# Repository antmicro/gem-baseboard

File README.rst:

GEM Demo Board
==============

Copyright (c) 2020 `Antmicro <https://www.antmicro.com>`_

.. image:: https://img.shields.io/badge/View%20on-Antmicro%20Open%20Source%20Portal-332d37?style=flat-square
      :target: https://opensource.antmicro.com/projects/gem-baseboard
   
.. figure:: img/gem-demo-board.png

This repository contains PCB design files for a demo board compatible with the `GEM1 <https://github.com/antmicro/gem1-adapter>`_ and `GEM2 <https://github.com/antmicro/gem2-adapter>`_ adapter boards.

The board acts as an evaluation carrier board for the GEM adapter boards.
It includes a 4-channel FTDI USB/MPSSE converter that can be used for configuring the chiplets inside the GEM designs from an external host PC using a single USB connection and the MPSSE engine built into the FTDI controller.

The board contains two FFC connectors supporting MIPI CSI input and output.
The FFC connectors are pin-compatible with the Raspberry Pi camera interface.
It is possible to connect a Raspberry Pi camera module to the input connector on the board and provide processed CSI data back on the output CSI FFC.
It is also possible to configure the board as an expansion hat for the Raspberry Pi platform.
For more details regarding the supported connection scenarios please refer to the respective schematic sheets.

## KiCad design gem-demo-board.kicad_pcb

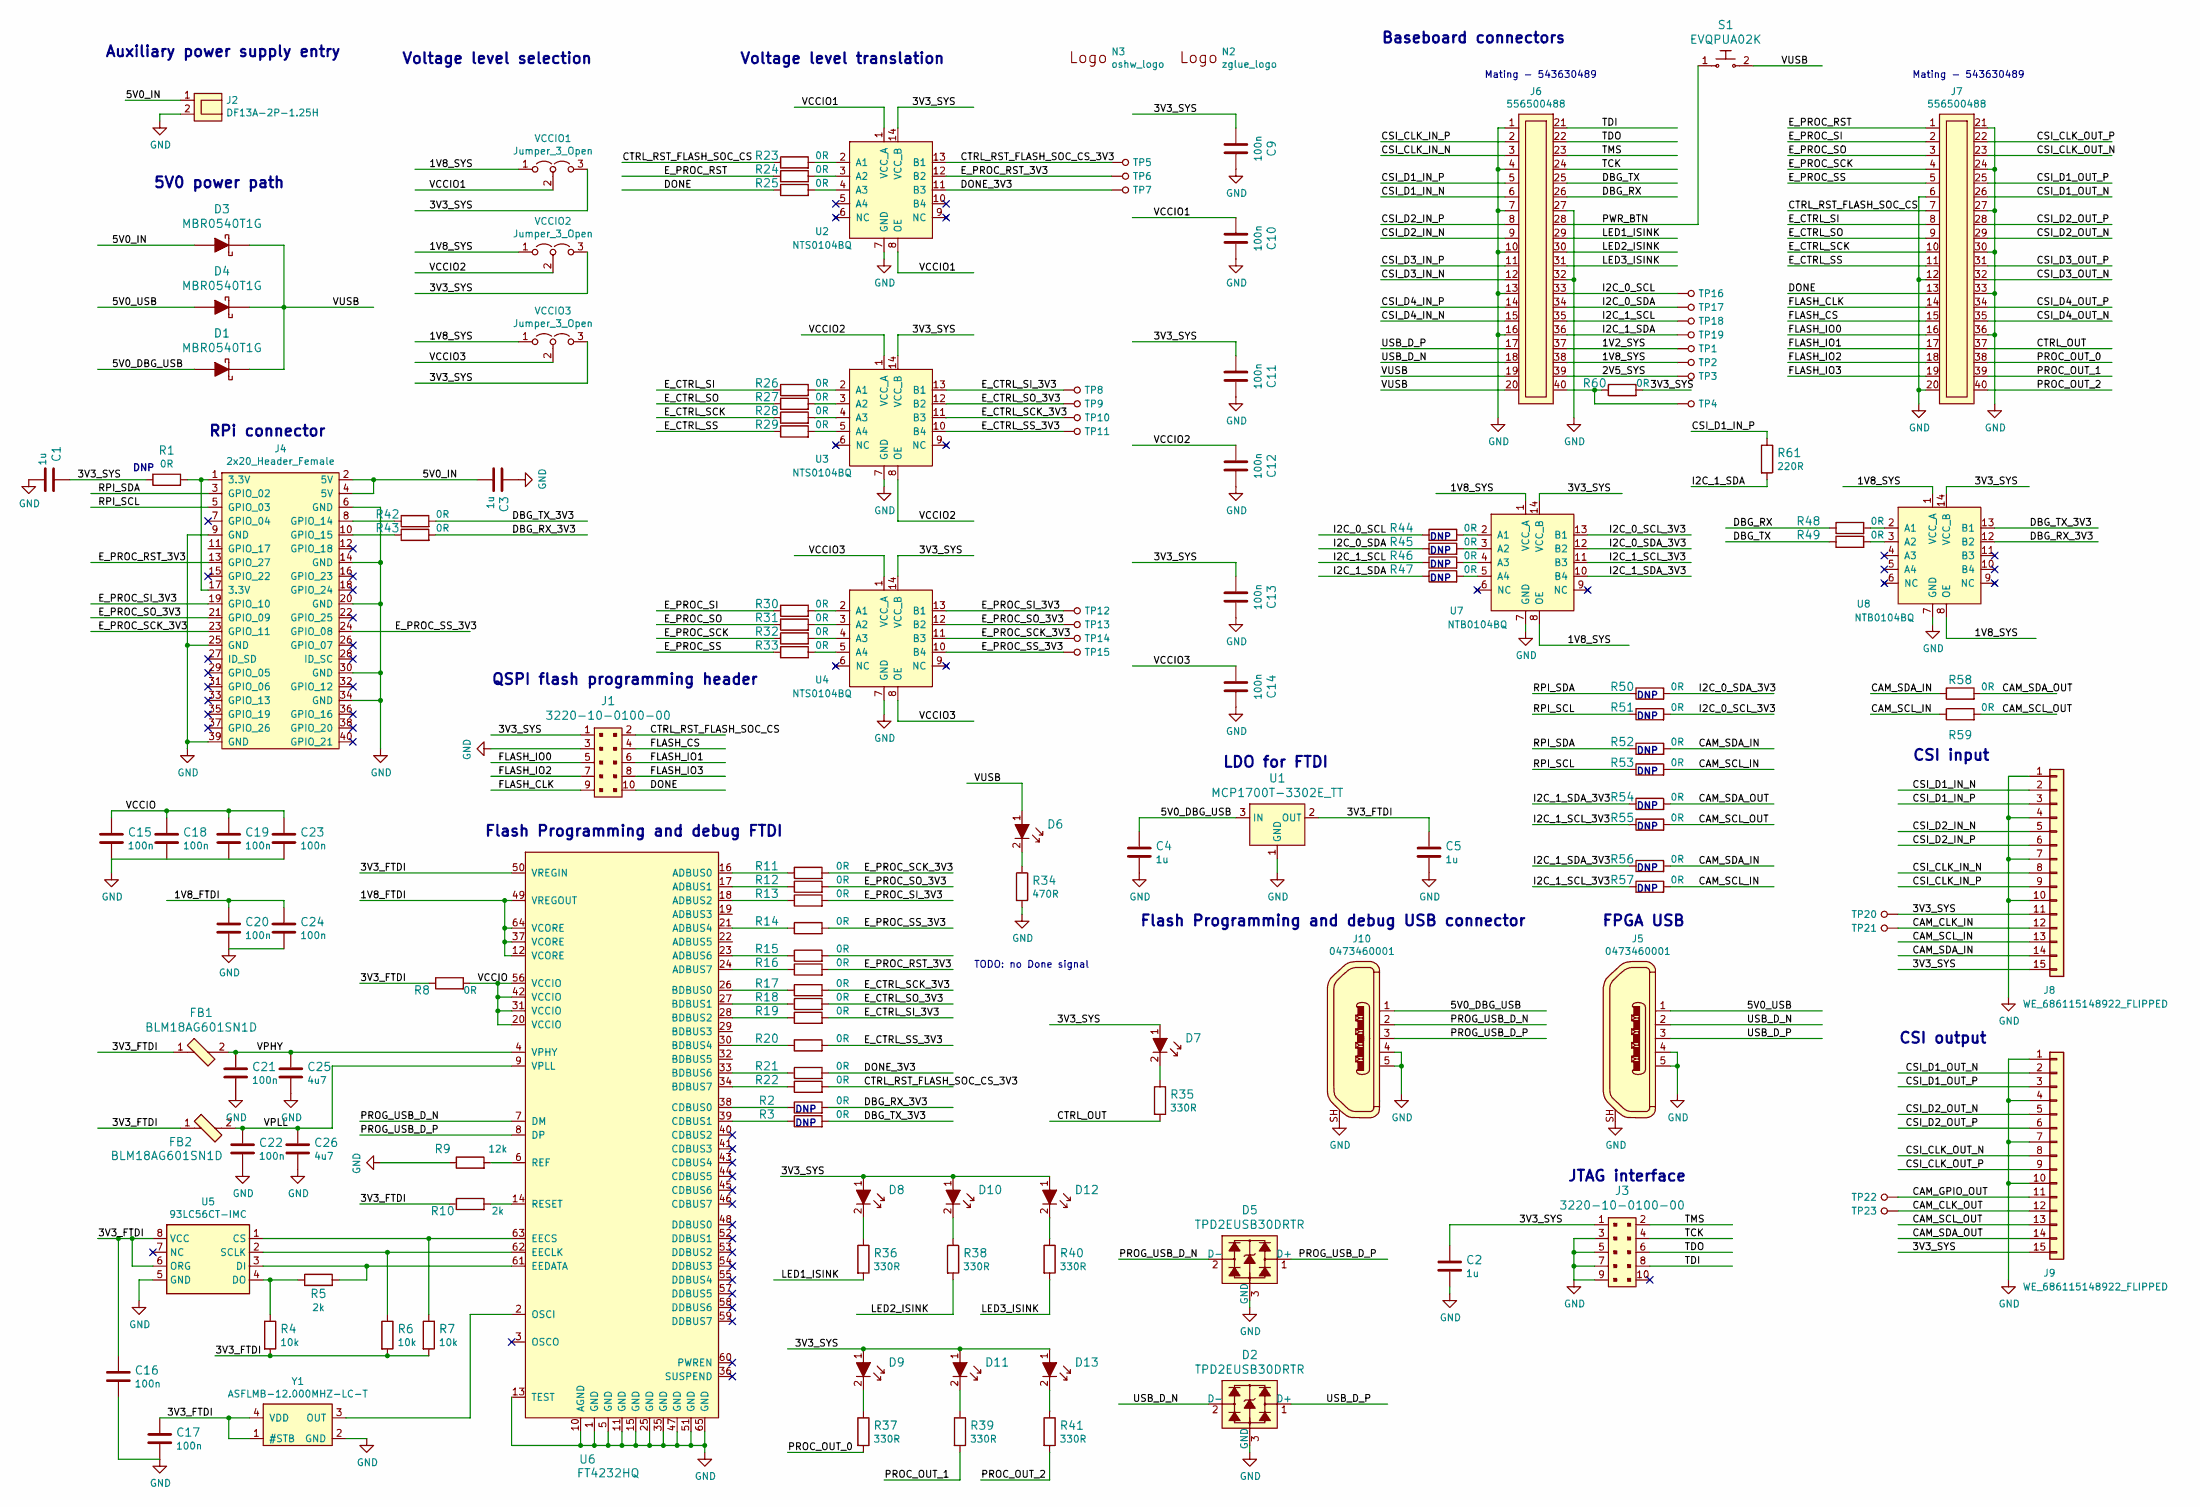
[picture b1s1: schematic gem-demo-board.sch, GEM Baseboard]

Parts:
C1, C2, C3, C4, C5: C_1u_0603; 0603-cap; MPN 0603X105K160CT
C9, C10, C11, C12, C13, C14, C15, C16, C17, C18, C19, C20, C21, C22, C23, C24: C_100n_0402_6V3; 0402-cap; MPN 0402X104K6R3CT
C25, C26: C_4u7_0402; 0402-cap; MPN GRM155R60G475ME
D1, D3, D4: MBR0540T1G; SOD-123; MPN MBR0540T1G
D2, D5: TPD2EUSB30DRTR; SOT-3; MPN TPD2EUSB30DRTR
D6, D7, D8, D9, D10, D11, D12, D13: LG_L29K-G2J1-24-Z; LED_0603; MPN LG L29K-G2J1-24-Z
FB1, FB2: BLM18AG601SN1D; 0603; MPN BLM18AG601SN1D
J1, J3: 3220-10-0100-00; PinHeader_2x5_P1.27mm_Drill.7mm; MPN 3220-10-0100-00
J2: DF13A-2P-1.25H; MPN DF13A-2P-1.25H
J4: 2x20_Header_Female; PinHeader_2x40_P2.54_Drill1mm; MPN 2214S-40SG-85
J5, J10: 0473460001; USB_Micro_B_Female_0473460001; MPN 0473460001
J6, J7: 556500488; MPN 556500488
J8, J9: WE_686115148922_FLIPPED; MPN 686115148922
N2: zglue_logo; zglue-logo
N3: oshw_logo; oshw-logo
R1: R_0R_0603; 0603-res; MPN CR0603-J/-000ELF
R2, R3, R8, R11, R12, R13, R14, R15, R16, R17, R18, R19, R20, R21, R22, R23, R24, R25, R26, R27, R28, R29, R30, R31, R32, R33, R42, R43, R44, R45, R46, R47, R48, R49, R50, R51, R52, R53, R54, R55, R56, R57, R58, R59, R60: R_0R_0402; 0402-res; MPN ERJ2GE0R00X
R4, R6, R7: R_10k_0402; 0402-res; MPN CRCW040210K0FKEDHP
R5, R10: R_2k_0402; 0402-res; MPN CRCW04022K00FKED
R9: R_12k_0402; 0402-res; MPN CRCW040212K0FKEDHP
R34: R_470R_0402; 0402-res; MPN CRCW0402470RFKED.
R35, R36, R37, R38, R39, R40, R41: R_330R_0402; 0402-res; MPN MCMR04X3300FTL
R61: R_220R_0402; 0402-res; MPN CRG0402J220R
S1: EVQPUA02K; Panasonic_EVQPUJ_EVQPUA; MPN EVQPUA02K
TP1, TP2, TP3, TP4, TP5, TP6, TP7, TP8, TP9, TP10, TP11, TP12, TP13, TP14, TP15, TP16, TP17, TP18, TP19, TP20, TP21, TP22, TP23: TP_SMD1MM; Testpoint_smd_1mm
U1: MCP1700T-3302E_TT; SOT-23-3; MPN MCP1700T-3302E/TT
U2, U3, U4: NTS0104BQ; QDHVQFN14; MPN NTS0104BQ
U5: 93LC56CT-IMC; DFN-8_2x3mm; MPN 93LC56CT-I/MC
U6: FT4232HQ; MPN FT4232HQ
U7, U8: NTB0104BQ; QDHVQFN14; MPN NTB0104BQ
VCCIO1, VCCIO2, VCCIO3: Jumper_3_Open; SolderJumper-3_P1.3mm_Open_Pad1.0x1.5mm
Y1: ASFLMB-12.000MHZ-LC-T; ASFLMB; MPN ASFLMB-12.000MHZ-LC-T

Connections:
/1V2_SYS: J6.37, TP1.1
/1V8_FTDI: C20.1, C24.1, U6.12 (VCORE), U6.37 (VCORE), U6.49 (VREGOUT), U6.64 (VCORE)
/1V8_SYS: J6.38, TP2.1, U7.1 (VCC_A), U7.8 (OE), U8.1 (VCC_A), U8.8 (OE), VCCIO1.1 (A), VCCIO2.1 (A), VCCIO3.1 (A)
/2V5_SYS: J6.39, TP3.1
/3V3_FTDI: C5.1, C16.1, C17.1, FB1.1, FB2.1, R4.2, R6.2, R7.2, R8.1, R10.1, U1.2 (OUT), U5.6 (ORG), U5.8 (VCC), U6.50 (VREGIN), Y1.1 (#STB), Y1.4 (VDD)
/3V3_SYS: C1.1, C2.1, C9.2, C11.2, C13.2, D7.1, D8.1, D9.1, D10.1, D11.1, D12.1, D13.1, J1.1, J3.1, J8.11, J8.15, J9.15, R1.1, R60.2, TP20.1, U2.14 (VCC_B), U3.14 (VCC_B), U4.14 (VCC_B), U7.14 (VCC_B), U8.14 (VCC_B), VCCIO1.3 (B), VCCIO2.3 (B), VCCIO3.3 (B)
/5V0_DBG_USB: C4.1, D1.A, J10.1, U1.3 (IN)
/5V0_IN: C3.2, D3.A, J2.1, J4.2 (5V), J4.4 (5V)
/5V0_USB: D4.A, J5.1
/CAM_CLK_IN: J8.12, TP21.1
/CAM_CLK_OUT: J9.12, TP23.1
/CAM_GPIO_OUT: J9.11, TP22.1
/CAM_SCL_IN: J8.13, R53.2, R57.2, R59.1
/CAM_SCL_OUT: J9.13, R55.2, R59.2
/CAM_SDA_IN: J8.14, R52.2, R56.2, R58.1
/CAM_SDA_OUT: J9.14, R54.2, R58.2
/CSI_CLK_IN_N: J6.3, J8.8
/CSI_CLK_IN_P: J6.2, J8.9
/CSI_CLK_OUT_N: J7.23, J9.8
/CSI_CLK_OUT_P: J7.22, J9.9
/CSI_D1_IN_N: J6.6, J8.2
/CSI_D1_IN_P: J6.5, J8.3, R61.1
/CSI_D1_OUT_N: J7.26, J9.2
/CSI_D1_OUT_P: J7.25, J9.3
/CSI_D2_IN_N: J6.9, J8.5
/CSI_D2_IN_P: J6.8, J8.6
/CSI_D2_OUT_N: J7.29, J9.5
/CSI_D2_OUT_P: J7.28, J9.6
/CSI_D3_IN_N: J6.12
/CSI_D3_IN_P: J6.11
/CSI_D3_OUT_N: J7.32
/CSI_D3_OUT_P: J7.31
/CSI_D4_IN_N: J6.15
/CSI_D4_IN_P: J6.14
/CSI_D4_OUT_N: J7.35
/CSI_D4_OUT_P: J7.34
/CTRL_OUT: J7.37, R35.2
/CTRL_RST_FLASH_SOC_CS: J1.2, J7.7, R23.1
/CTRL_RST_FLASH_SOC_CS_3V3: R22.2, TP5.1, U2.13 (B1)
/DBG_RX: J6.26, R48.1
/DBG_RX_3V3: R2.2, R43.2, U8.12 (B2)
/DBG_TX: J6.25, R49.1
/DBG_TX_3V3: R3.2, R42.2, U8.13 (B1)
/DONE: J1.10, J7.13, R25.1
/DONE_3V3: R21.2, TP7.1, U2.11 (B3)
/E_CTRL_SCK: J7.10, R28.1
/E_CTRL_SCK_3V3: R17.2, TP10.1, U3.11 (B3)
/E_CTRL_SI: J7.8, R26.1
/E_CTRL_SI_3V3: R19.2, TP8.1, U3.13 (B1)
/E_CTRL_SO: J7.9, R27.1
/E_CTRL_SO_3V3: R18.2, TP9.1, U3.12 (B2)
/E_CTRL_SS: J7.11, R29.1
/E_CTRL_SS_3V3: R20.2, TP11.1, U3.10 (B4)
/E_PROC_RST: J7.1, R24.1
/E_PROC_RST_3V3: J4.13 (GPIO_27), R16.2, TP6.1, U2.12 (B2)
/E_PROC_SCK: J7.4, R32.1
/E_PROC_SCK_3V3: J4.23 (GPIO_11), R11.2, TP14.1, U4.11 (B3)
/E_PROC_SI: J7.2, R30.1
/E_PROC_SI_3V3: J4.19 (GPIO_10), R13.2, TP12.1, U4.13 (B1)
/E_PROC_SO: J7.3, R31.1
/E_PROC_SO_3V3: J4.21 (GPIO_09), R12.2, TP13.1, U4.12 (B2)
/E_PROC_SS: J7.5, R33.1
/E_PROC_SS_3V3: J4.24 (GPIO_08), R14.2, TP15.1, U4.10 (B4)
/FLASH_CLK: J1.9, J7.14
/FLASH_CS: J1.4, J7.15
/FLASH_IO0: J1.5, J7.16
/FLASH_IO1: J1.6, J7.17
/FLASH_IO2: J1.7, J7.18
/FLASH_IO3: J1.8, J7.19
/I2C_0_SCL: J6.33, R44.1, TP16.1
/I2C_0_SCL_3V3: R51.2, U7.13 (B1)
/I2C_0_SDA: J6.34, R45.1, TP17.1
/I2C_0_SDA_3V3: R50.2, U7.12 (B2)
/I2C_1_SCL: J6.35, R46.1, TP18.1
/I2C_1_SCL_3V3: R55.1, R57.1, U7.11 (B3)
/I2C_1_SDA: J6.36, R47.1, R61.2, TP19.1
/I2C_1_SDA_3V3: R54.1, R56.1, U7.10 (B4)
/LED1_ISINK: J6.29, R36.2
/LED2_ISINK: J6.30, R38.2
/LED3_ISINK: J6.31, R40.2
/PROC_OUT_0: J7.38, R37.2
/PROC_OUT_1: J7.39, R39.2
/PROC_OUT_2: J7.40, R41.2
/PROG_USB_D_N: D5.2 (D-), J10.2, U6.7 (DM)
/PROG_USB_D_P: D5.1 (D+), J10.3, U6.8 (DP)
/PWR_BTN: J6.28, S1.1
/RPI_SCL: J4.5 (GPIO_03), R51.1, R53.1
/RPI_SDA: J4.3 (GPIO_02), R50.1, R52.1
/TCK: J3.4, J6.24
/TDI: J3.8, J6.21
/TDO: J3.6, J6.22
/TMS: J3.2, J6.23
/USB_D_N: D2.2 (D-), J5.2, J6.18
/USB_D_P: D2.1 (D+), J5.3, J6.17
/VCCIO: C15.1, C18.1, C19.1, C23.1, R8.2, U6.20 (VCCIO), U6.31 (VCCIO), U6.42 (VCCIO), U6.56 (VCCIO)
/VCCIO1: C10.2, U2.1 (VCC_A), U2.8 (OE), VCCIO1.2 (C)
/VCCIO2: C12.2, U3.1 (VCC_A), U3.8 (OE), VCCIO2.2 (C)
/VCCIO3: C14.2, U4.1 (VCC_A), U4.8 (OE), VCCIO3.2 (C)
/VPHY: C21.1, C25.1, FB1.2, U6.4 (VPHY)
/VPLL: C22.1, C26.1, FB2.2, U6.9 (VPLL)
/VUSB: D1.K, D3.K, D4.K, D6.1, J6.19, J6.20, S1.2
GND: C1.2, C2.2, C3.1, C4.2, C5.2, C9.1, C10.1, C11.1, C12.1, C13.1, C14.1, C15.2, C16.2, C17.2, C20.2, C21.2, C22.2, C23.2, C24.2, C25.2, C26.2, D2.3 (GND), D5.3 (GND), J1.3, J2.2, J3.3, J3.5, J3.7, J3.9, J4.6 (GND), J4.9 (GND), J4.14 (GND), J4.20 (GND), J4.25 (GND), J4.30 (GND), J4.34 (GND), J4.39 (GND), J5.4, J5.5, J5.SH, J6.1, J6.4, J6.7, J6.10, J6.13, J6.16, J6.27, J6.32, J7.6, J7.12, J7.20, J7.21, J7.24, J7.27, J7.30, J7.33, J7.36, J8.1, J8.4, J8.7, J8.10, J9.1, J9.4, J9.7, J9.10, J10.4, J10.5, J10.SH, R9.1, R34.2, U1.1 (GND), U2.7 (GND), U3.7 (GND), U4.7 (GND), U5.5 (GND), U6.1 (GND), U6.5 (GND), U6.10 (AGND), U6.11 (GND), U6.13 (TEST), U6.15 (GND), U6.25 (GND), U6.35 (GND), U6.47 (GND), U6.51 (GND), U6.65 (GND), U7.7 (GND), U8.7 (GND), Y1.2 (GND)
unnamed: D6.2, R34.1
unnamed: D7.2, R35.1
unnamed: D8.2, R36.1
unnamed: D9.2, R37.1
unnamed: D10.2, R38.1
unnamed: D11.2, R39.1
unnamed: D12.2, R40.1
unnamed: D13.2, R41.1
unnamed: J4.1 (3.3V), J4.17 (3.3V), R1.2
unnamed: J4.8 (GPIO_14), R42.1
unnamed: J4.10 (GPIO_15), R43.1
unnamed: J6.40, R60.1, TP4.1
unnamed: R2.1, U6.38 (CDBUS0)
unnamed: R3.1, U6.39 (CDBUS1)
unnamed: R4.1, R5.1, U5.4 (DO)
unnamed: R5.2, U5.3 (DI), U6.61 (EEDATA)
unnamed: R6.1, U5.2 (SCLK), U6.62 (EECLK)
unnamed: R7.1, U5.1 (CS), U6.63 (EECS)
unnamed: R9.2, U6.6 (REF)
unnamed: R10.2, U6.14 (RESET)
unnamed: R11.1, U6.16 (ADBUS0)
unnamed: R12.1, U6.17 (ADBUS1)
unnamed: R13.1, U6.18 (ADBUS2)
unnamed: R14.1, U6.21 (ADBUS4)
unnamed: R15.1, U6.23 (ADBUS6)
unnamed: R16.1, U6.24 (ADBUS7)
unnamed: R17.1, U6.26 (BDBUS0)
unnamed: R18.1, U6.27 (BDBUS1)
unnamed: R19.1, U6.28 (BDBUS2)
unnamed: R20.1, U6.30 (BDBUS4)
unnamed: R21.1, U6.33 (BDBUS6)
unnamed: R22.1, U6.34 (BDBUS7)
unnamed: R23.2, U2.2 (A1)
unnamed: R24.2, U2.3 (A2)
unnamed: R25.2, U2.4 (A3)
unnamed: R26.2, U3.2 (A1)
unnamed: R27.2, U3.3 (A2)
unnamed: R28.2, U3.4 (A3)
unnamed: R29.2, U3.5 (A4)
unnamed: R30.2, U4.2 (A1)
unnamed: R31.2, U4.3 (A2)
unnamed: R32.2, U4.4 (A3)
unnamed: R33.2, U4.5 (A4)
unnamed: R44.2, U7.2 (A1)
unnamed: R45.2, U7.3 (A2)
unnamed: R46.2, U7.4 (A3)
unnamed: R47.2, U7.5 (A4)
unnamed: R48.2, U8.2 (A1)
unnamed: R49.2, U8.3 (A2)
unnamed: U6.2 (OSCI), Y1.3 (OUT)

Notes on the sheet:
Baseboard connectors
Auxiliary power supply entry
RPi connector
JTAG interface
FPGA USB
5V0 power path
CSI input
CSI output
Mating - 543630489
Voltage level translation
Flash Programming and debug USB connector
Flash Programming and debug FTDI
TODO: no Done signal
LDO for FTDI
Voltage level selection
QSPI flash programming header
DNP

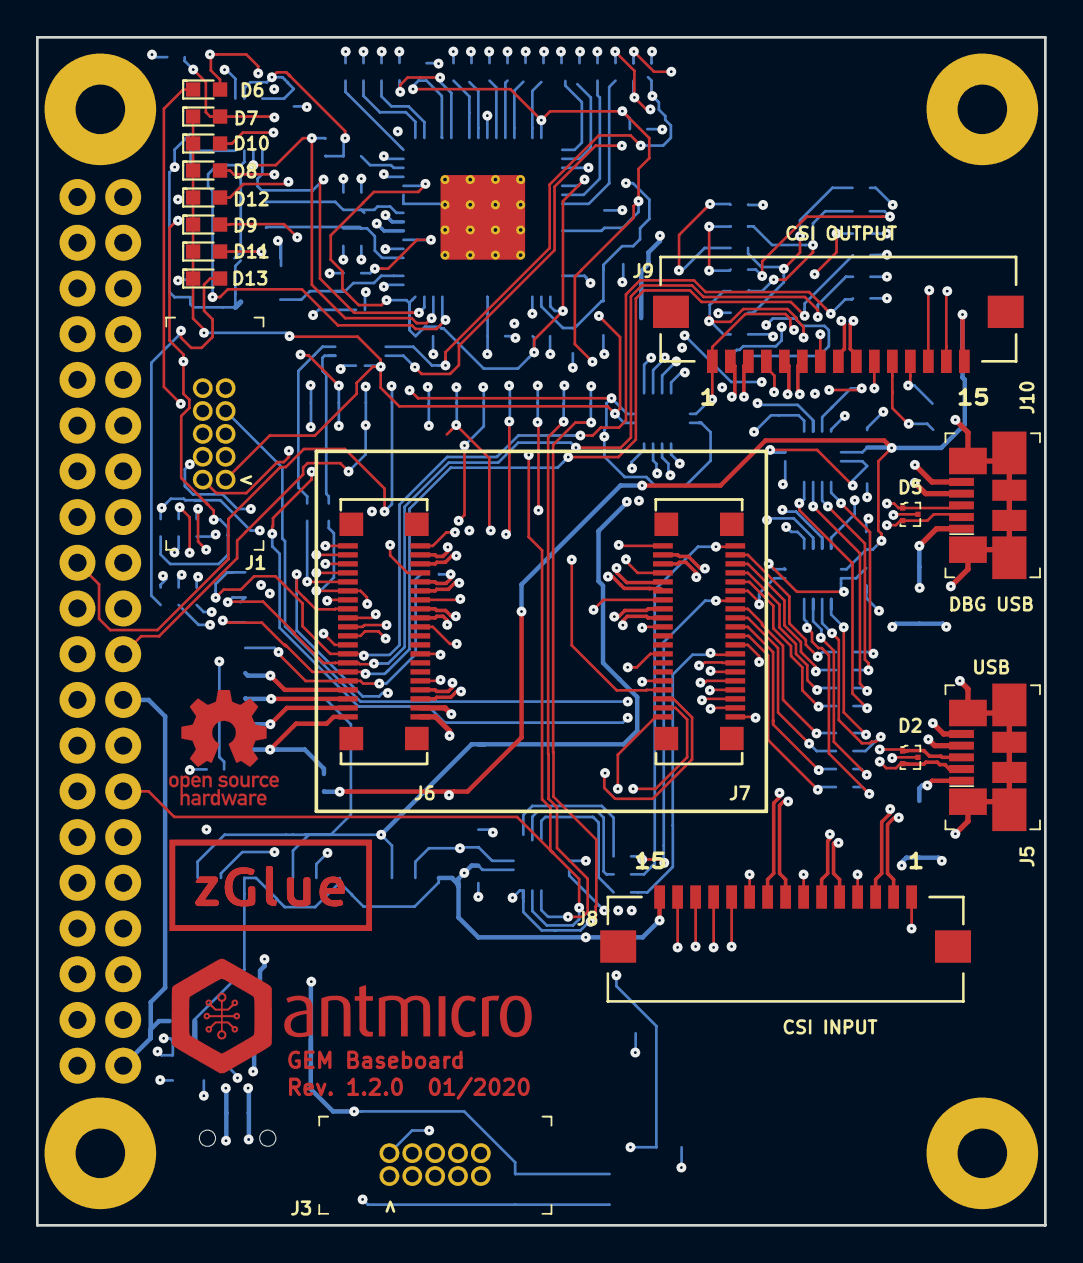
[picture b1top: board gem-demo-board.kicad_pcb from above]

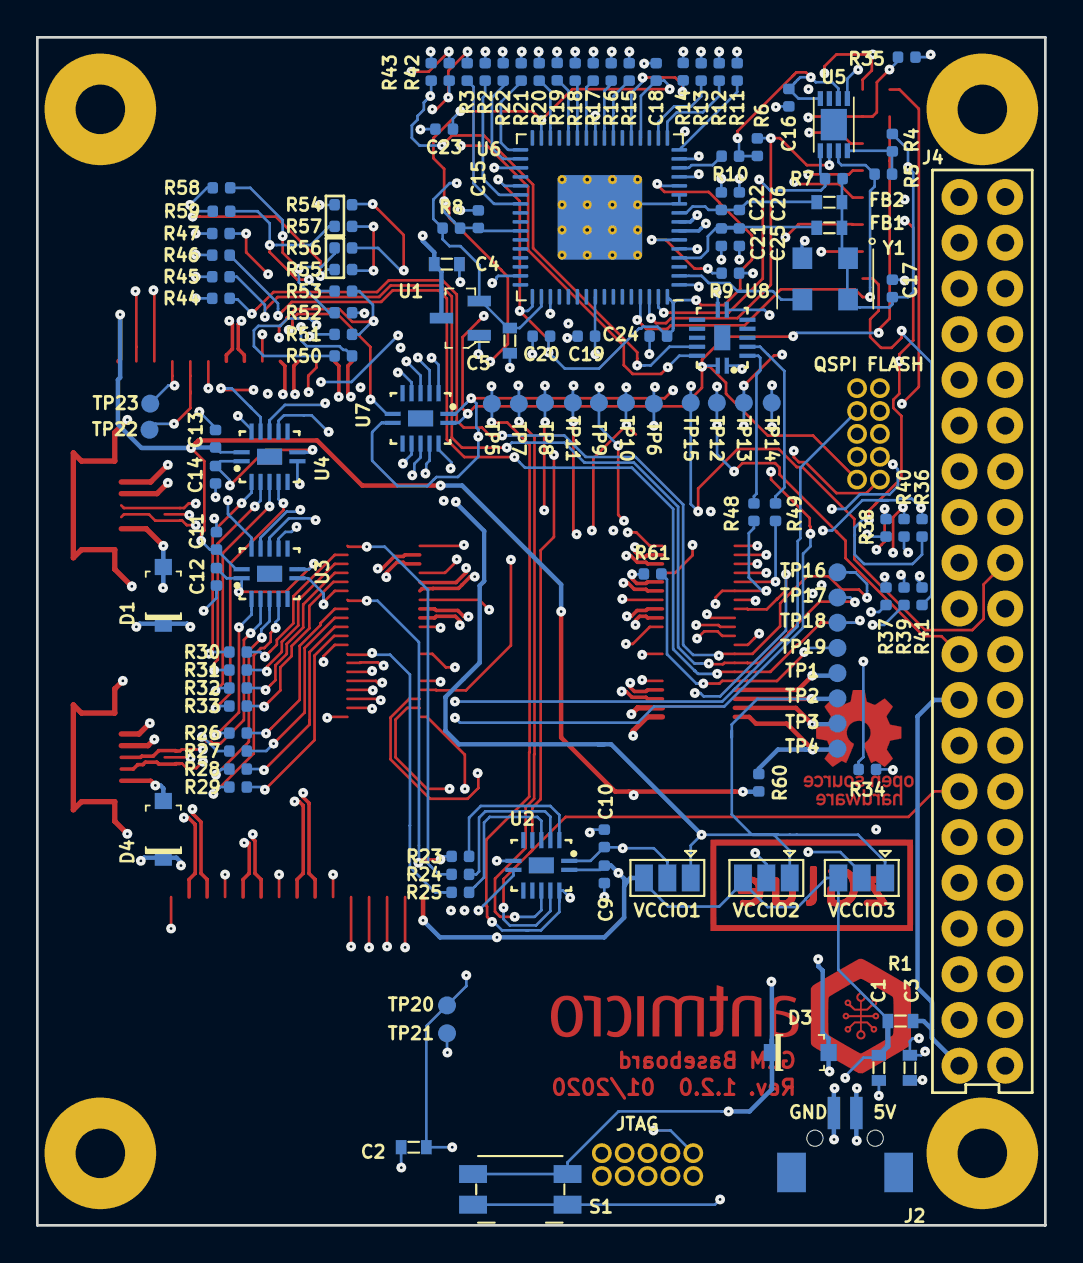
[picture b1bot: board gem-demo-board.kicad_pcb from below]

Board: 6 copper layers, 56.0 x 66.0 mm, 149 parts (127 on the bottom side), 144 nets.

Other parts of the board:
N1: antmicro_logo; antmicro-logo_scaled_20mm
N2#2: zglue_logo; zglue-logo

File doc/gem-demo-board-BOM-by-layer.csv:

Reference,Quantity,Value,Footprint,Manufacturer,MPN,Layer,
D10 D11 D12 D13 D6 D7 D8 D9,8,LG_L29K-G2J1-24-Z,LED_0603,OSRAM Opto Semiconductors Inc.,LG L29K-G2J1-24-Z,Top,
D2 D5,2,TPD2EUSB30DRTR,SOT-3,Texas Instruments,TPD2EUSB30DRTR,Top,
J1 J3,2,3220-10-0100-00,PinHeader_2x5_P1.27mm_Drill.7mm,CNC Tech,3220-10-0100-00,Top,
J10 J5,2,0473460001,USB_Micro_B_Female_0473460001,Molex,0473460001,Top,
J6 J7,2,556500488,556500488,Molex,556500488,Top,
J8 J9,2,WE_686115148922_FLIPPED,WE_686115148922_FLIPPED,Wurth Elektronik ,686115148922,Top,
C1 C2 C3 C4 C5,5,C_1u_0603,0603-cap,WALSIN,0603X105K160CT,Bottom,
C10 C11 C12 C13 C14 C15 C16 C17 C18 C19 C20 C21 C22 C23 C24 C9,16,C_100n_0402_6V3,0402-cap,Walsin,0402X104K6R3CT,Bottom,
C25 C26,2,C_4u7_0402,0402-cap,MURATA,GRM155R60G475ME,Bottom,
D1 D3 D4,3,MBR0540T1G,SOD-123,ON Semiconductor,MBR0540T1G,Bottom,
FB1 FB2,2,BLM18AG601SN1D,0603,Murata Electronics North America,BLM18AG601SN1D,Bottom,
J2,1,DF13A-2P-1.25H,DF13A-2P-1.25H,Hirose,DF13A-2P-1.25H,Bottom,
J4,1,2x20_Header_Female,PinHeader_2x40_P2.54_Drill1mm,MULTICOMP,2214S-40SG-85 ,Bottom,
R1,1,R_0R_0603,0603-res,BOURNS,CR0603-J/-000ELF,Bottom,
R10 R5,2,R_2k_0402,0402-res,VISHAY,CRCW04022K00FKED,Bottom,
R11 R12 R13 R14 R15 R16 R17 R18 R19 R2 R20 R21 R22 R23 R24 R25 R26 R27 R28 R29 R3 R30 R31 R32 R33 R42 R43 R48 R49 R58 R59 R60 R8,33,R_0R_0402,0402-res,PANASONIC,ERJ2GE0R00X,Bottom,
R34,1,R_470R_0402,0402-res,VISHAY,CRCW0402470RFKED.,Bottom,
R35 R36 R37 R38 R39 R40 R41,7,R_330R_0402,0402-res,MULTICOMP,MCMR04X3300FTL,Bottom,
R4 R6 R7,3,R_10k_0402,0402-res,VISHAY,CRCW040210K0FKEDHP,Bottom,
R61,1,R_220R_0402,0402-res,TE_CONNECTIVITY_/_NEOHM,CRG0402J220R,Bottom,
R9,1,R_12k_0402,0402-res,VISHAY,CRCW040212K0FKEDHP,Bottom,
S1,1,EVQPUA02K,Panasonic_EVQPUJ_EVQPUA,Panasonic,EVQPUA02K,Bottom,
U1,1,MCP1700T-3302E_TT,SOT-23-3,Microchip Technology,MCP1700T-3302E/TT,Bottom,
U2 U3 U4,3,NTS0104BQ,QDHVQFN14,NXP Semiconductors,NTS0104BQ,Bottom,
U5,1,93LC56CT-IMC,DFN-8_2x3mm,Microchip,93LC56CT-I/MC,Bottom,
U6,1,FT4232HQ,FT4232HQ,FTDI,FT4232HQ,Bottom,
U7 U8,2,NTB0104BQ,QDHVQFN14,NXP Semiconductors,NTB0104BQ,Bottom,
Y1,1,ASFLMB-12.000MHZ-LC-T,ASFLMB,TXC,7C-24.000MBB-T,Bottom,
R44 R45 R46 R47 R50 R51 R52 R53 R54 R55 R56 R57,12,R_0R_0402,0402-res,PANASONIC,ERJ2GE0R00X,DNP,
N2,1,zglue_logo,zglue-logo,,,Virtual,
N3,1,oshw_logo,oshw-logo,,,Virtual,
TP1 TP10 TP11 TP12 TP13 TP14 TP15 TP16 TP17 TP18 TP19 TP2 TP20 TP21 TP22 TP23 TP3 TP4 TP5 TP6 TP7 TP8 TP9,23,TP_SMD1MM,Testpoint_smd_1mm,,,Virtual,
VCCIO1 VCCIO2 VCCIO3,3,Jumper_3_Open-Jumper,,,,Virtual,

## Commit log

2019-10-11 added FT4232
2019-10-11 Exported PDF schematic
2019-10-14 fixed power path
2019-10-14 unified 3V3 voltage rails
2019-10-14 schematic cleanup
2019-10-15 finished initial component placement, some minor changes in schematics related to footprints
2019-10-15 generated fresh schematic pdf
2019-10-17 rotated adapter board footprint by 180 deg
2019-10-22 finished routing
2019-10-23 tuned differential pairs lengths
2019-10-23 added programming header for QSPI flash
2019-11-04 added LEDs and power button
2019-11-05 added mounting holes
2019-11-06 added some connections for I2C and UART
2020-02-19 Finished initial component placement
2020-02-19 Added BOM
2020-02-19 Added connections for I2C and UART
2020-02-19 Schematic updated after initial bringup
2020-02-19 Generated schematic pdf
2020-02-19 Tuned differential pairs
2020-02-19 Started revision 1.1, moved components to bottom side
2020-02-19 Routing finished
2020-02-19 Added .gitignore
2020-02-19 Tied SPI signals for programming second FPGA from RPi
2020-02-19 PCB cleanup, updated layout
2020-02-19 Connected PWR_BTN to VUSB, updated PCB
2020-02-19 Gerber files used for PCB manufacturing
2020-02-19 Layout components moved away from PCB edges
2020-02-19 Cleanup of DRC issues
2020-02-19 Updated rev. number and date
2020-02-19 Disconnected 3v3_sys from GEM system chip with R60
2020-02-19 Minor updates on PCB
2020-02-19 Exported R_220R to local library
2020-02-19 Connect CSI_D1_IN_P to I2C_1_SDA through R61
2020-02-19 Minor changes
2020-02-19 Flipped CSI input connector
    Use camera FFC with pads on the same side now
2020-02-19 Moved JTAG connector
2020-06-08 Fixed MPN for 12Mhz oscillator
2020-06-08 Updated Project Name
2020-06-08 Cleanup
2020-06-08 Updated revision marking
2020-06-08 Add documentation for release
2020-10-01 Update photo
2021-06-24 Notes added by 'git notes add'
2022-05-27 Scale image
2022-05-27 Add badge
